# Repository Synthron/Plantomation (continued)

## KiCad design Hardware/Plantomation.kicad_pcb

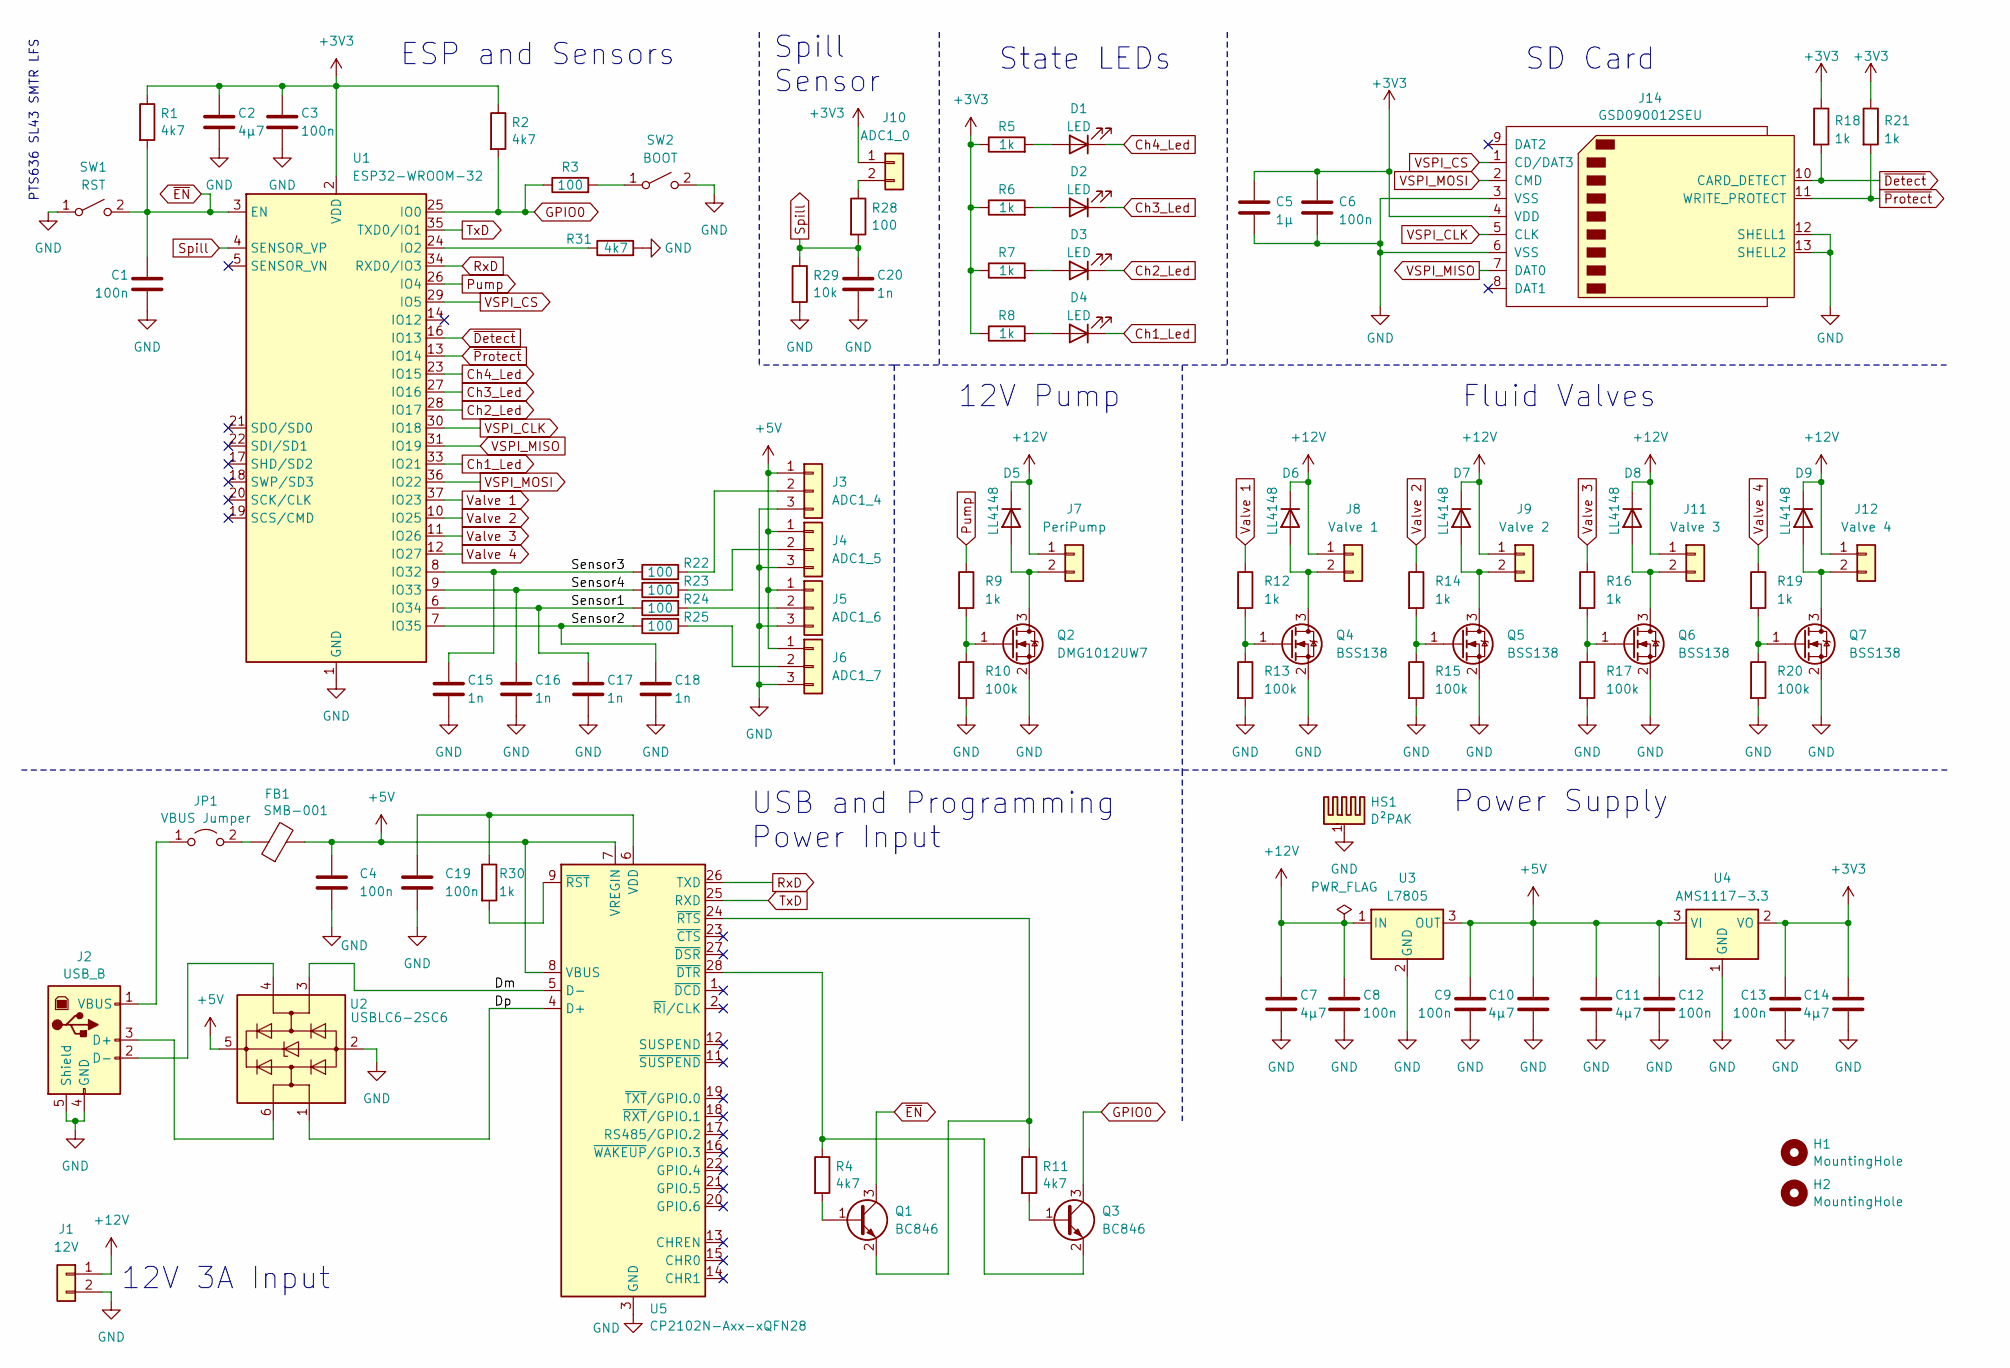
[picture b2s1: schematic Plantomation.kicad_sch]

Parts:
C1, C3, C4, C6, C8, C9, C12, C13, C19: 100n; C_0805_2012Metric
C2, C7, C10, C11, C14: 4µ7; C_0805_2012Metric
C5: 1µ; C_0805_2012Metric
C15, C16, C17, C18, C20: 1n; C_0805_2012Metric
D1, D2, D3, D4: LED; LED_0805_2012Metric
D5, D6, D7, D8, D9: LL4148; D_MiniMELF
FB1: SMB-001; SMB-002
H1, H2: MountingHole; MountingHole_3.2mm_M3
HS1: D²PAK; Heatsink_Fischer_FK24413DPAK_23x13mm
J1: 12V; JST_XH_B2B-XH-A_1x02_P2.50mm_Vertical
J2: USB_B; USB_B_Lumberg_2411_02_Horizontal
J3: ADC1_4; JST_XH_B3B-XH-A_1x03_P2.50mm_Vertical
J4: ADC1_5; JST_XH_B3B-XH-A_1x03_P2.50mm_Vertical
J5: ADC1_6; JST_XH_B3B-XH-A_1x03_P2.50mm_Vertical
J6: ADC1_7; JST_XH_B3B-XH-A_1x03_P2.50mm_Vertical
J7: PeriPump; JST_XH_B2B-XH-A_1x02_P2.50mm_Vertical
J8: Valve 1; JST_XH_B2B-XH-A_1x02_P2.50mm_Vertical
J9: Valve 2; JST_XH_B2B-XH-A_1x02_P2.50mm_Vertical
J10: ADC1_0; JST_XH_B2B-XH-A_1x02_P2.50mm_Vertical
J11: Valve 3; JST_XH_B2B-XH-A_1x02_P2.50mm_Vertical
J12: Valve 4; JST_XH_B2B-XH-A_1x02_P2.50mm_Vertical
J14: GSD090012SEU
JP1: VBUS Jumper; PinHeader_1x02_P2.54mm_Vertical
Q1, Q3: BC846; SOT-23
Q2: DMG1012UW7; SOT-23
Q4, Q5, Q6, Q7: BSS138; SOT-23
R1, R2, R4, R11, R31: 4k7; R_0805_2012Metric
R3, R22, R23, R24, R25, R28: 100; R_0805_2012Metric
R5, R6, R7, R8, R9, R12, R14, R16, R18, R19, R21, R30: 1k; R_0805_2012Metric
R10, R13, R15, R17, R20: 100k; R_0805_2012Metric
R29: 10k; R_0805_2012Metric
SW1: RST; SW_Tactile_SPST_NO_Straight_CK_PTS636Sx25SMTRLFS
SW2: BOOT; SW_Tactile_SPST_NO_Straight_CK_PTS636Sx25SMTRLFS
U1: ESP32-WROOM-32
U2: USBLC6-2SC6; SOT-23-6
U3: L7805; TO-252-2
U4: AMS1117-3.3; SOT-223-3_TabPin2
U5: CP2102N-Axx-xQFN28; QFN-28-1EP_5x5mm_P0.5mm_EP3.35x3.35mm

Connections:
+3V3: C2.1, C3.1, C5.1, C6.1, C13.1, C14.1, J10.1, J14.4 (VDD), R1.1, R2.1, R5.1, R6.1, R7.1, R8.1, R18.1, R21.1, U1.2 (VDD), U4.2 (VO)
+5V: C4.1, C9.1, C10.1, C11.1, C12.1, FB1.2, J3.1, J4.1, J5.1, J6.1, U2.5 (VBUS), U3.3 (OUT), U4.3 (VI), U5.7 (VREGIN), U5.8 (VBUS)
+12V: C7.1, C8.1, D5.1 (K), D6.1 (K), D7.1 (K), D8.1 (K), D9.1 (K), J1.1, J7.1, J8.1, J9.1, J11.1, J12.1, U3.1 (IN)
/Dm: U2.3 (I/O2), U5.5 (D-)
/Dp: U2.1 (I/O1), U5.4 (D+)
/Sensor1: C17.1, R24.1, U1.6 (IO34)
/Sensor2: C18.1, R25.1, U1.7 (IO35)
/Sensor3: C15.1, R22.1, U1.8 (IO32)
/Sensor4: C16.1, R23.1, U1.9 (IO33)
Ch1_Led: D4.1 (K), U1.33 (IO21)
Ch2_Led: D3.1 (K), U1.28 (IO17)
Ch3_Led: D2.1 (K), U1.27 (IO16)
Ch4_Led: D1.1 (K), U1.23 (IO15)
GND: C1.2, C2.2, C3.2, C4.2, C5.2, C6.2, C7.2, C8.2, C9.2, C10.2, C11.2, C12.2, C13.2, C14.2, C15.2, C16.2, C17.2, C18.2, C19.2, C20.2, HS1.1, J1.2, J2.4 (GND), J2.5 (Shield), J3.3, J4.3, J5.3, J6.3, J14.3 (VSS), J14.6 (VSS), J14.12 (SHELL1), J14.13 (SHELL2), Q2.2 (S), Q4.2 (S), Q5.2 (S), Q6.2 (S), Q7.2 (S), R10.2, R13.2, R15.2, R17.2, R20.2, R29.2, R31.2, SW1.1 (A), SW2.2 (B), U1.1 (GND), U1.15 (GND), U1.38 (GND), U1.39 (GND), U2.2 (GND), U3.2 (GND), U4.1 (GND), U5.3 (GND), U5.29 (GND)
GPIO0: Q3.3 (C), R2.2, R3.1, U1.25 (IO0)
unnamed: D1.2 (A), R5.2
unnamed: D2.2 (A), R6.2
unnamed: D3.2 (A), R7.2
unnamed: D4.2 (A), R8.2
unnamed: D5.2 (A), J7.2, Q2.3 (D)
unnamed: D6.2 (A), J8.2, Q4.3 (D)
unnamed: D7.2 (A), J9.2, Q5.3 (D)
unnamed: D8.2 (A), J11.2, Q6.3 (D)
unnamed: D9.2 (A), J12.2, Q7.3 (D)
unnamed: J2.3 (D+), U2.6 (I/O1)
unnamed: J2.2 (D-), U2.4 (I/O2)
unnamed: J2.1 (VBUS), JP1.1 (A)
unnamed: J3.2, R22.2
unnamed: J4.2, R23.2
unnamed: J5.2, R24.2
unnamed: J6.2, R25.2
unnamed: J10.2, R28.1
unnamed: FB1.1, JP1.2 (B)
unnamed: Q1.1 (B), R4.2
unnamed: Q1.2 (E), R11.1, U5.24 (~RTS)
unnamed: Q2.1 (G), R9.2, R10.1
unnamed: Q3.1 (B), R11.2
unnamed: Q3.2 (E), R4.1, U5.28 (~DTR)
unnamed: Q4.1 (G), R12.2, R13.1
unnamed: Q5.1 (G), R14.2, R15.1
unnamed: Q6.1 (G), R16.2, R17.1
unnamed: Q7.1 (G), R19.2, R20.1
unnamed: R3.2, SW2.1 (A)
unnamed: R31.1, U1.24 (IO2)
unnamed: C19.1, R30.1, U5.6 (VDD)
unnamed: R30.2, U5.9 (~RST)
Pump: R9.1, U1.26 (IO4)
RxD: U1.34 (RXD0/IO3), U5.26 (TXD)
Spill: C20.1, R28.2, R29.1, U1.4 (SENSOR_VP)
TxD: U1.35 (TXD0/IO1), U5.25 (RXD)
VSPI_CLK: J14.5 (CLK), U1.30 (IO18)
VSPI_CS: J14.1 (CD/DAT3), U1.29 (IO5)
VSPI_MISO: J14.7 (DAT0), U1.31 (IO19)
VSPI_MOSI: J14.2 (CMD), U1.36 (IO22)
Valve 1: R12.1, U1.37 (IO23)
Valve 2: R14.1, U1.10 (IO25)
Valve 3: R16.1, U1.11 (IO26)
Valve 4: R19.1, U1.12 (IO27)
~Detect: J14.10 (CARD_DETECT), R18.2, U1.16 (IO13)
~EN: C1.1, Q1.3 (C), R1.2, SW1.2 (B), U1.3 (EN)
~Protect: J14.11 (WRITE_PROTECT), R21.2, U1.13 (IO14)

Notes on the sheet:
State LEDs
12V 3A Input
Fluid Valves
ESP and Sensors
12V Pump
SD Card
Power Supply
USB and Programming Power Input
Spill Sensor
PTS636 SL43 SMTR LFS

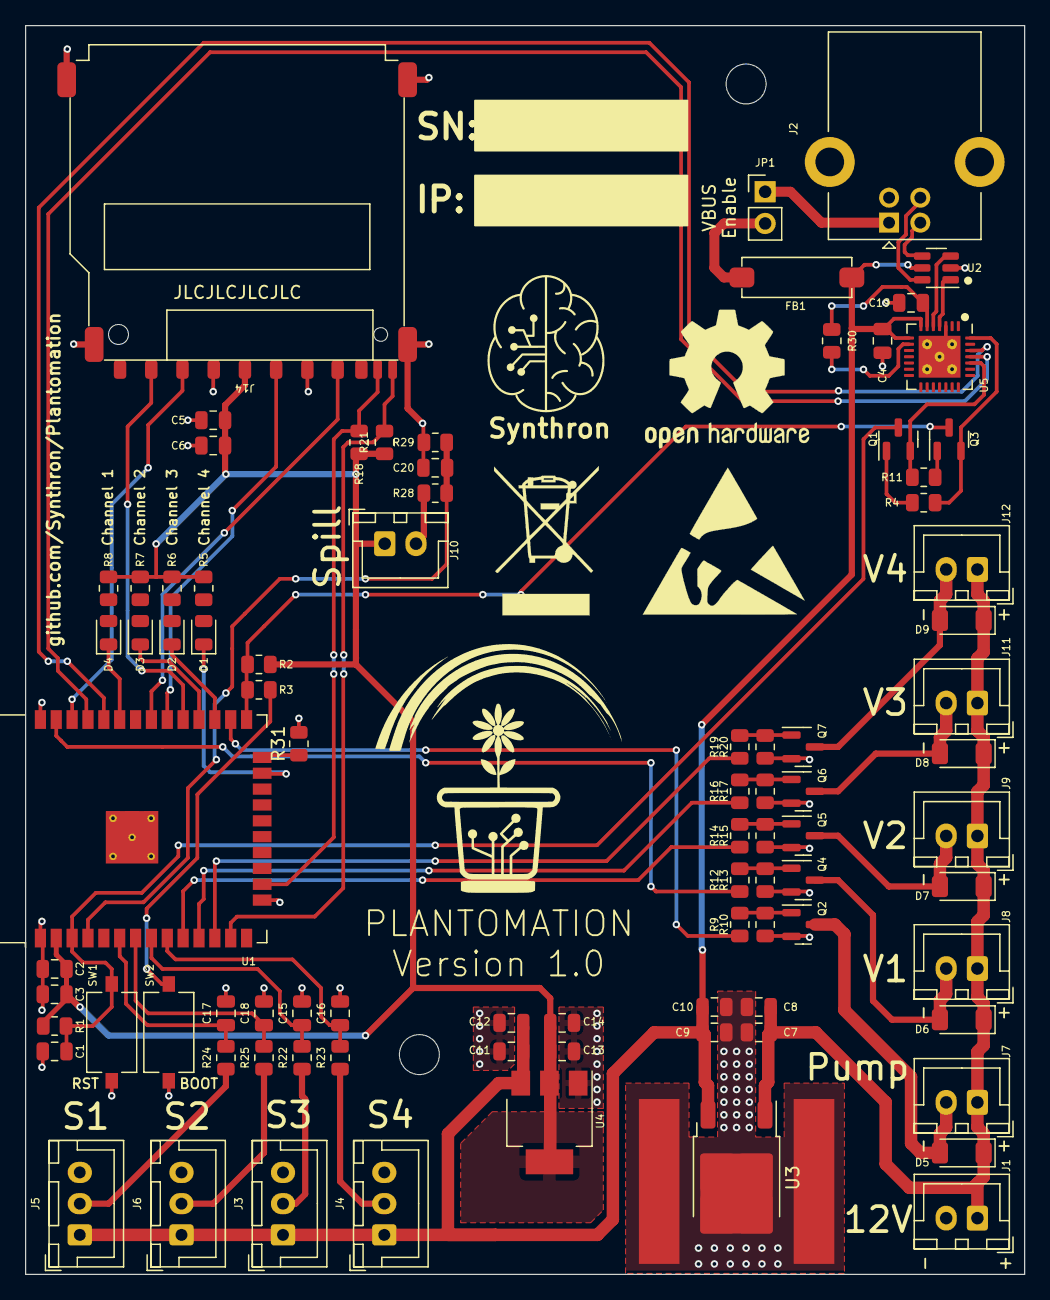
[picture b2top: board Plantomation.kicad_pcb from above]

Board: 2 copper layers, 80.0 x 100.0 mm, 90 parts (0 on the bottom side), 61 nets.

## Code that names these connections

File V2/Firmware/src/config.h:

#pragma one

#define DOUT    1
#define DCLK    2
#define DLATCH  3
#define CS2     4
#define CS3     5
#define SDA     6
#define SCL     7
#define CS1     8
#define CS0     10
#define SCK     12
#define MISO    13
#define MOSI    14
#define TxD1    17
#define RxD1    18
#define DIR     38
#define DETECT  47
#define CS4     48

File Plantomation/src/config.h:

/**
 * 
 * Global config file for Plantomation
 * 
 * Pin Definitions, Label definitions and 
 * Compile-Options like debug and resetting the SPIFFS
 * 
*/

#pragma once

#ifndef CONFIG_H
#define CONFIG_H

// Pin Definitions
#define pump 4
#define SD_CS 5
#define detect 13
#define protect 14
#define LED1 21
#define LED2 17
#define LED3 16
#define LED4 15
#define v1 23
#define v2 25
#define v3 26
#define v4 27
// Sensor Value between 1.5V (in water) and 2.8V (dry air);
#define s1 34
#define s2 35
#define s3 32
#define s4 33
#define spill 36

// Defines for Webinterface
#define SYS_OK 0
#define SYS_SPILL 1
#define SYS_FAIL 2
#define SYS_SD 3
#define SYS_EMPTY 4
#define SYS_FATAL 255

//miscellaneous
#define pump_volume 0
#define pump_time 1
#define samplecount 10

//file paths
#define spiffs_wifi_conf "/wifi.json"
#define spiffs_system_conf "/control.json"
#define spiffs_plant1_conf "/plant1.json"
#define spiffs_plant2_conf "/plant2.json"
#define spiffs_plant3_conf "/plant3.json"
#define spiffs_plant4_conf "/plant4.json"

#define sd_wifi_conf "/config/wifi.json"
#define sd_system_conf "/config/control.json"
#define sd_plant1_conf "/config/plant1.json"
#define sd_plant2_conf "/config/plant2.json"
#define sd_plant3_conf "/config/plant3.json"
#define sd_plant4_conf "/config/plant4.json"
#define sd_plant1_logs "/log/plant1.log"
#define sd_plant2_logs "/log/plant2.log"
#define sd_plant3_logs "/log/plant3.log"
#define sd_plant4_logs "/log/plant4.log"
#define sd_events_logs "/log/events.log"

#define watering_time 5

#define moist_dry 3400
#define moist_wet 1600

#define FORMAT_SPIFFS_IF_FAILED false


#endif //  CONFIG_H

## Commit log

2023-11-26 Layout finalization
2023-11-27 Finishing Touches on Layout before Review
2023-11-28 codebase and first part review
2023-11-29 Big Repo Overhaul Started Documentation First Review Overhaul of Schematic and Layout First working Test Code for webpage and OTA
2023-11-30 Update main.h
    cleaned up html code, enabled Ajax scripting
2023-11-30 Update main.cpp
    implement Ajax, clean up async server handling
2023-11-30 testing
2023-11-30 Finalizing PCB and Review Firmware Bugfixes for Ajax Firmware get a working responsive page layout
2023-12-01 add debug environment
2023-12-01 add credentials file in gitignore to hide
2023-12-03 Config Update 1 update doc for configuration files still needs new update for json instead of xml update code to use AP mode when no config or wifi
2023-12-03 edit sites.h
2023-12-03 Code Update create classes make parametric main page according to channel state use json builder instead of sprintf in Ajax general cleanup
2023-12-03 Add ToDo list to Readme
2023-12-03 add documentation to ToDo
2023-12-04 add schematic PDF
2023-12-05 documentation update
2023-12-06 Code Update Divide main.cpp into several different files NOT COMPILING
2023-12-06 attempted fix: extern for global instances, didn't work
2023-12-09 code overhaul add about page section
2023-12-10 minor changes added favicon added explanatories to header files
2024-01-11 Major Code Update implement SD implement sensors expand config page implement file system on SD implement debug level implement log level
2024-01-11 Bugfix for gefault SSID
2024-01-11 bugfix boot message order
2024-03-05 Add V2, Cleanup Repo
2024-03-17 prepare code and 3d files
2024-04-07 V1: Critical Code Fix preventing correct working
2024-06-03 Start Code for V2
2024-06-15 Fix Upload Issues
